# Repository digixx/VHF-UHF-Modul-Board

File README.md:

# VHF-UHF-Modul-Board

This board helps to use SA8x8 VHF/UHF transceiver modules in any projects. It supports an adjustable MIC-Amp and Speaker-Amp. You can choose between a classic microphone or digital output of an mikrocontroller. It is 5V friendly and has LEDs for most signals.

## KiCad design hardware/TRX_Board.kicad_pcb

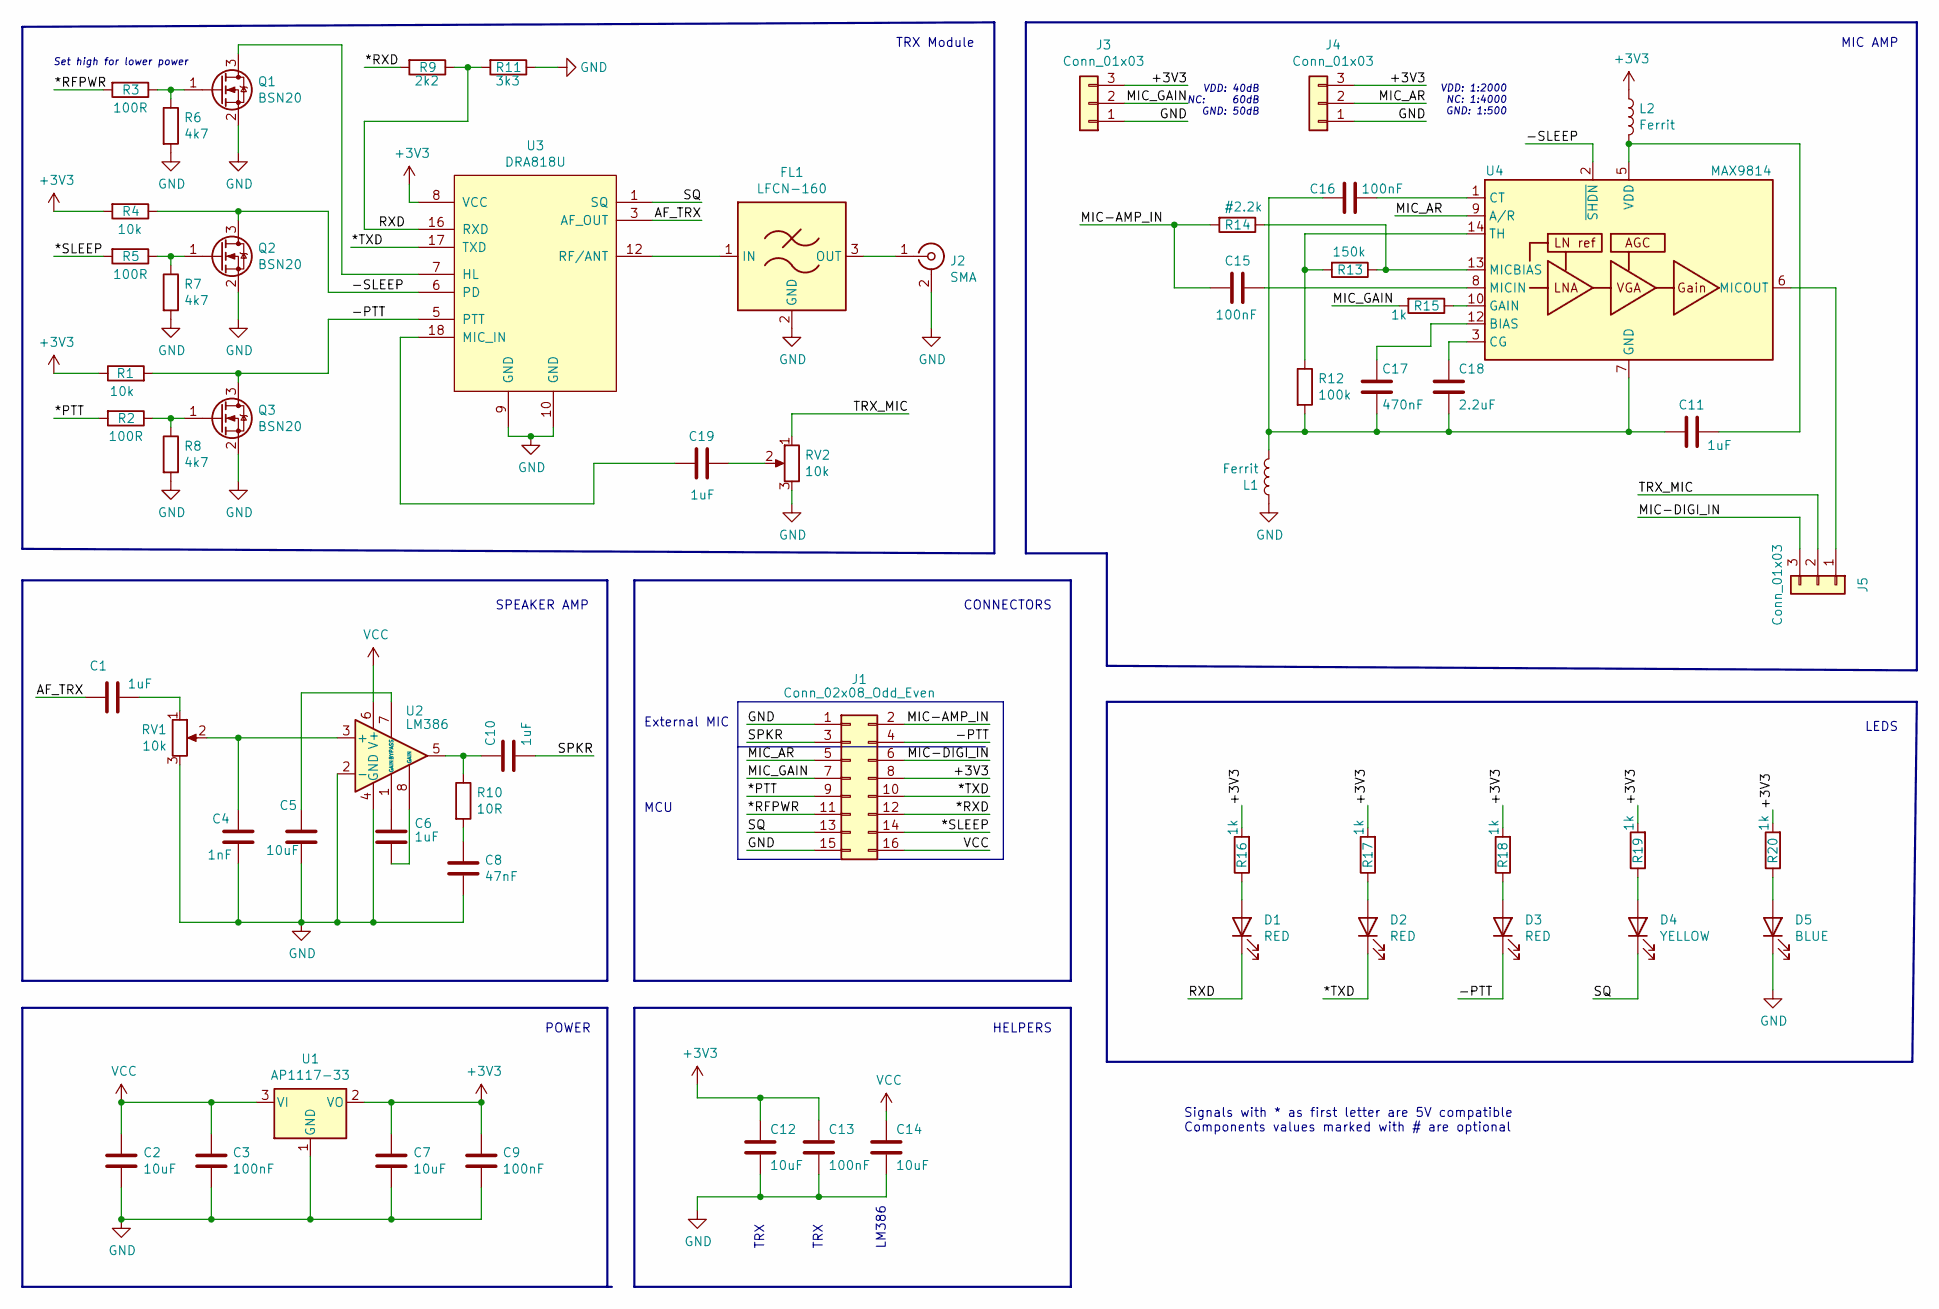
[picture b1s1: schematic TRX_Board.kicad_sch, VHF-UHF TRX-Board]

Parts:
C1, C6, C10, C11, C19: 1uF; C_0805_2012Metric; LCSC C28323
C2, C5, C7, C12, C14: 10uF; C_0805_2012Metric; LCSC C15850
C3, C9, C13, C15, C16: 100nF; C_0805_2012Metric; LCSC C49678
C4: 1nF; C_0805_2012Metric; LCSC C46653
C8: 47nF; C_0805_2012Metric; LCSC C53134
C17: 470nF; C_0805_2012Metric; LCSC C13967
C18: 2.2uF; C_0805_2012Metric; LCSC C49217
D1, D2, D3: RED; LED_0603_1608Metric; LCSC C2286
D4: YELLOW; LED_0603_1608Metric; LCSC C2296
D5: BLUE; LED_0603_1608Metric; LCSC C12624
FL1: LFCN-160; Filter_Mini-Circuits_FV1206
J1: Conn_02x08_Odd_Even; PinHeader_2x08_P2.54mm_Vertical
J2: SMA; SMA_Amphenol_132134-16_Vertical
J3, J4: Conn_01x03; PinHeader_1x03_P2.54mm_Vertical
J5: Conn_01x03; SolderJumper-3_P2.0mm_Open_TrianglePad1.0x1.5mm_NumberLabels
L1, L2: Ferrit; R_0805_2012Metric_Pad1.20x1.40mm_HandSolder
Q1, Q2, Q3: BSN20; SOT-23; LCSC C20917
R1, R4: 10k; R_0805_2012Metric; LCSC C17414
R2, R3, R5: 100R; R_0805_2012Metric; LCSC C17408
R6, R7, R8: 4k7; R_0805_2012Metric; LCSC C17673
R9: 2k2; R_0805_2012Metric; LCSC C17520
R10: 10R; R_0805_2012Metric; LCSC C17415
R11: 3k3; R_0805_2012Metric; LCSC C26010
R12: 100k; R_0805_2012Metric; LCSC C17407
R13: 150k; R_0805_2012Metric; LCSC C17470
R14: #2.2k; R_0805_2012Metric; LCSC C17520
R15, R16, R17, R18, R19, R20: 1k; R_0805_2012Metric; LCSC C17513
RV1, RV2: 10k; Potentiometer_Vishay_TS53YL_Vertical
U1: AP1117-33; SOT-223-3_TabPin2; LCSC C92517
U2: LM386; SOIC-8_3.9x4.9mm_P1.27mm; LCSC C23573
U3: DRA818U; DRA818
U4: MAX9814; DFN-14-1EP_3x3mm_P0.4mm_EP1.78x2.35mm; LCSC C41714

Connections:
+3V3: C7.1, C9.1, C12.1, C13.1, J1.8, J3.3, J4.3, L2.1, R1.1, R4.2, R16.2, R17.2, R18.2, R19.2, R20.2, U1.2 (VO), U3.8 (VCC)
/*PTT: J1.9, R2.2
/*RFPWR: J1.11, R3.2
/*RXD: J1.12, R9.2
/*SLEEP: J1.14, R5.2
/*TXD: D2.1 (K), J1.10, U3.17 (TXD)
/-PTT: D3.1 (K), J1.4, Q3.3 (D), R1.2, U3.5 (PTT)
/-SLEEP: Q2.3 (D), R4.1, U3.6 (PD), U4.2 (~SHDN)
/AF_TRX: C1.1, U3.3 (AF_OUT)
/MIC-AMP_IN: C15.2, J1.2, R14.2
/MIC-DIGI_IN: J1.6, J5.3
/MIC_AR: J1.5, J4.2, U4.9 (A/R)
/MIC_GAIN: J1.7, J3.2, R15.2
/RXD: D1.1 (K), R9.1, R11.2, U3.16 (RXD)
/SPKR: C10.2, J1.3
/SQ: D4.1 (K), J1.13, U3.1 (SQ)
/TRX_MIC: J5.2, RV2.1
GND: C2.2, C3.2, C4.2, C5.2, C7.2, C8.2, C9.2, C12.2, C13.2, C14.2, D5.1 (K), FL1.2 (GND), FL1.4 (GND), J1.1, J1.15, J2.2 (Ext), J3.1, J4.1, L1.1, Q1.2 (S), Q2.2 (S), Q3.2 (S), R6.2, R7.2, R8.2, R11.1, RV1.3, RV2.3, U1.1 (GND), U2.2 (-), U2.4 (GND), U3.9 (GND), U3.10 (GND)
unnamed: C1.2, RV1.1
unnamed: C4.1, RV1.2, U2.3 (+)
unnamed: C5.1, U2.7 (BYPASS)
unnamed: C6.1, U2.1 (GAIN)
unnamed: C6.2, U2.8 (GAIN)
unnamed: C8.1, R10.2
unnamed: C10.1, R10.1, U2.5
unnamed: C11.1, C16.1, C17.2, C18.2, L1.2, R12.2, U4.4 (GND), U4.7 (GND), U4.11 (GND), U4.15 (GND)
unnamed: C11.2, L2.2, U4.5 (VDD)
unnamed: C15.1, U4.8 (MICIN)
unnamed: C16.2, U4.1 (CT)
unnamed: C17.1, U4.12 (BIAS)
unnamed: C18.1, U4.3 (CG)
unnamed: C19.1, U3.18 (MIC_IN)
unnamed: C19.2, RV2.2
unnamed: D1.2 (A), R16.1
unnamed: D2.2 (A), R17.1
unnamed: D3.2 (A), R18.1
unnamed: D4.2 (A), R19.1
unnamed: D5.2 (A), R20.1
unnamed: FL1.1 (IN), U3.12 (RF/ANT)
unnamed: FL1.3 (OUT), J2.1 (In)
unnamed: Q1.1 (G), R3.1, R6.1
unnamed: Q1.3 (D), U3.7 (HL)
unnamed: Q2.1 (G), R5.1, R7.1
unnamed: Q3.1 (G), R2.1, R8.1
unnamed: R12.1, R13.2, U4.14 (TH)
unnamed: R13.1, R14.1, U4.13 (MICBIAS)
unnamed: R15.1, U4.10 (GAIN)
unnamed: J5.1, U4.6 (MICOUT)
VCC: C2.1, C3.1, C14.1, J1.16, U1.3 (VI), U2.6 (V+)

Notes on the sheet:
LEDS
VDD: 1:2000 NC: 1:4000 GND: 1:500
TRX Module
VDD: 40dB NC: 60dB GND: 50dB
External MIC
CONNECTORS
MCU
POWER
SPEAKER AMP
LM386
Set high for lower power
MIC AMP
TRX
Signals with * as first letter are 5V compatible Components values marked with # are optional
HELPERS

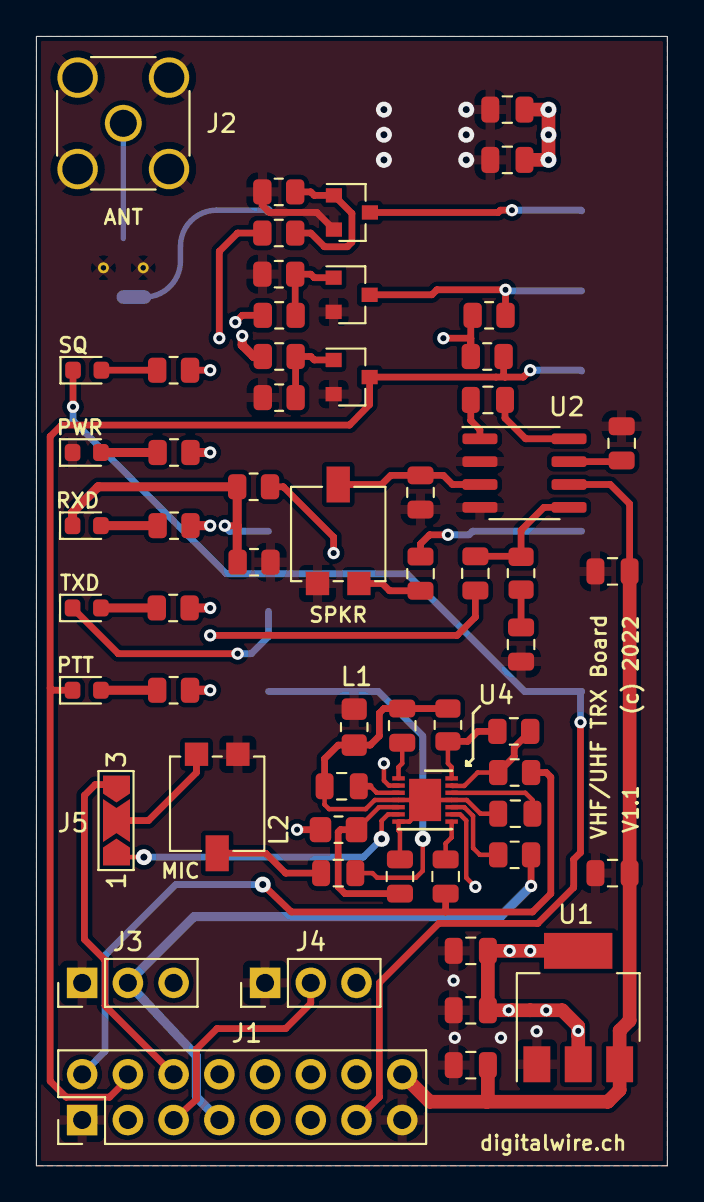
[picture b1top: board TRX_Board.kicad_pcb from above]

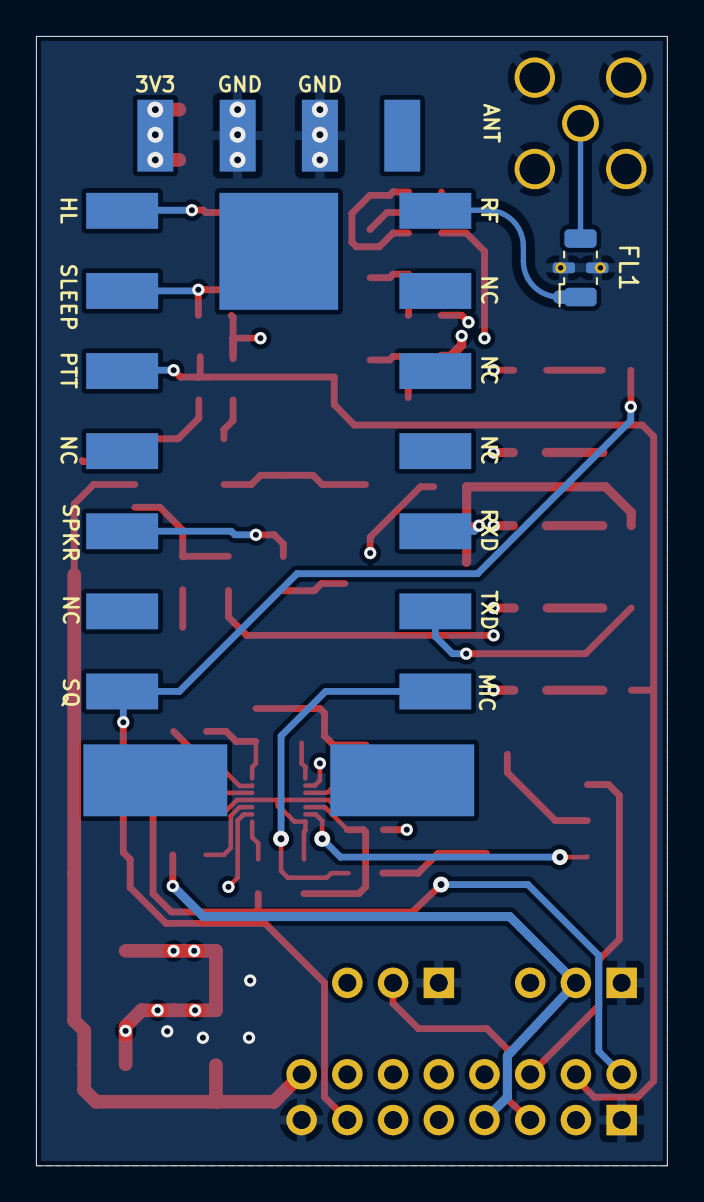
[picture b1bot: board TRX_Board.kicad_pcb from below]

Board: 4 copper layers, 35.1 x 62.7 mm, 61 parts (2 on the bottom side), 49 nets.

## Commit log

2021-12-26 Upgraded to KiCad V6, rearanged some parts, added silkscreen
2021-12-26 Changed page information
2021-12-26 added schemata and pcb as PDFs
2022-01-30 Changed Mic Input
    - Removed Poti near Mic
    - Added Poti and jumper near the module
2022-01-30 Create TRX_BoardV2.kicad_sch
    Including changes of the Mic input (changed position of potentiometer, added jumper)
2022-01-30 Added Labels
2022-01-30 Changed position of C on MICOUT of MAX...
2022-01-30 MIC input jumper labels changed
2022-01-30 New folder arrangement for better team working
2022-01-30 updated schematic for better mic support / added documents
2022-01-31 Optimized MIC path for electret and digital sources / added separated dirs for Gerbers
2022-01-31 new Gerbers for V1.1
2022-01-31 added schemata,pdf
2022-02-01 Changed traces to antenna to 50 ohms
2022-02-08 added Component Map
2022-02-28 Added missing parts sources
2022-04-15 Add modified BOM with categorized sections and updated part numbers
2022-04-15 ignore macos DS_Store files
2022-04-15 add 'sep=;' to csv file so that it can load properly in excel

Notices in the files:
hardware/TRX_Board.kicad_pcb:
(c) 2022
